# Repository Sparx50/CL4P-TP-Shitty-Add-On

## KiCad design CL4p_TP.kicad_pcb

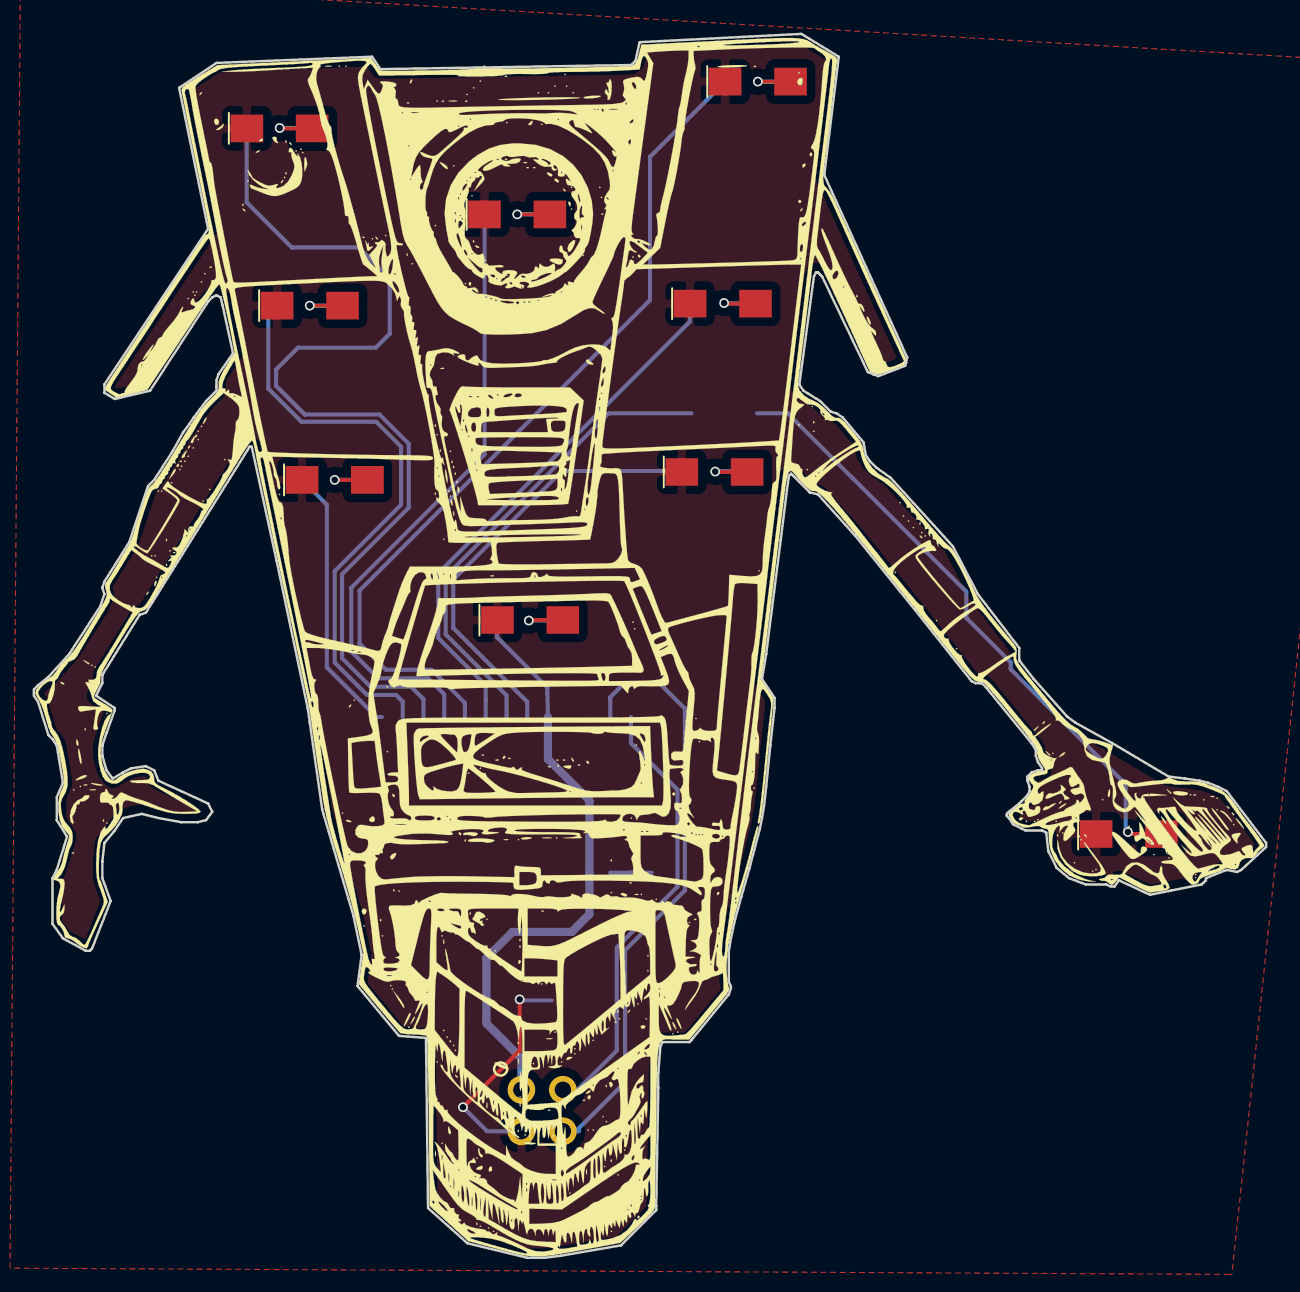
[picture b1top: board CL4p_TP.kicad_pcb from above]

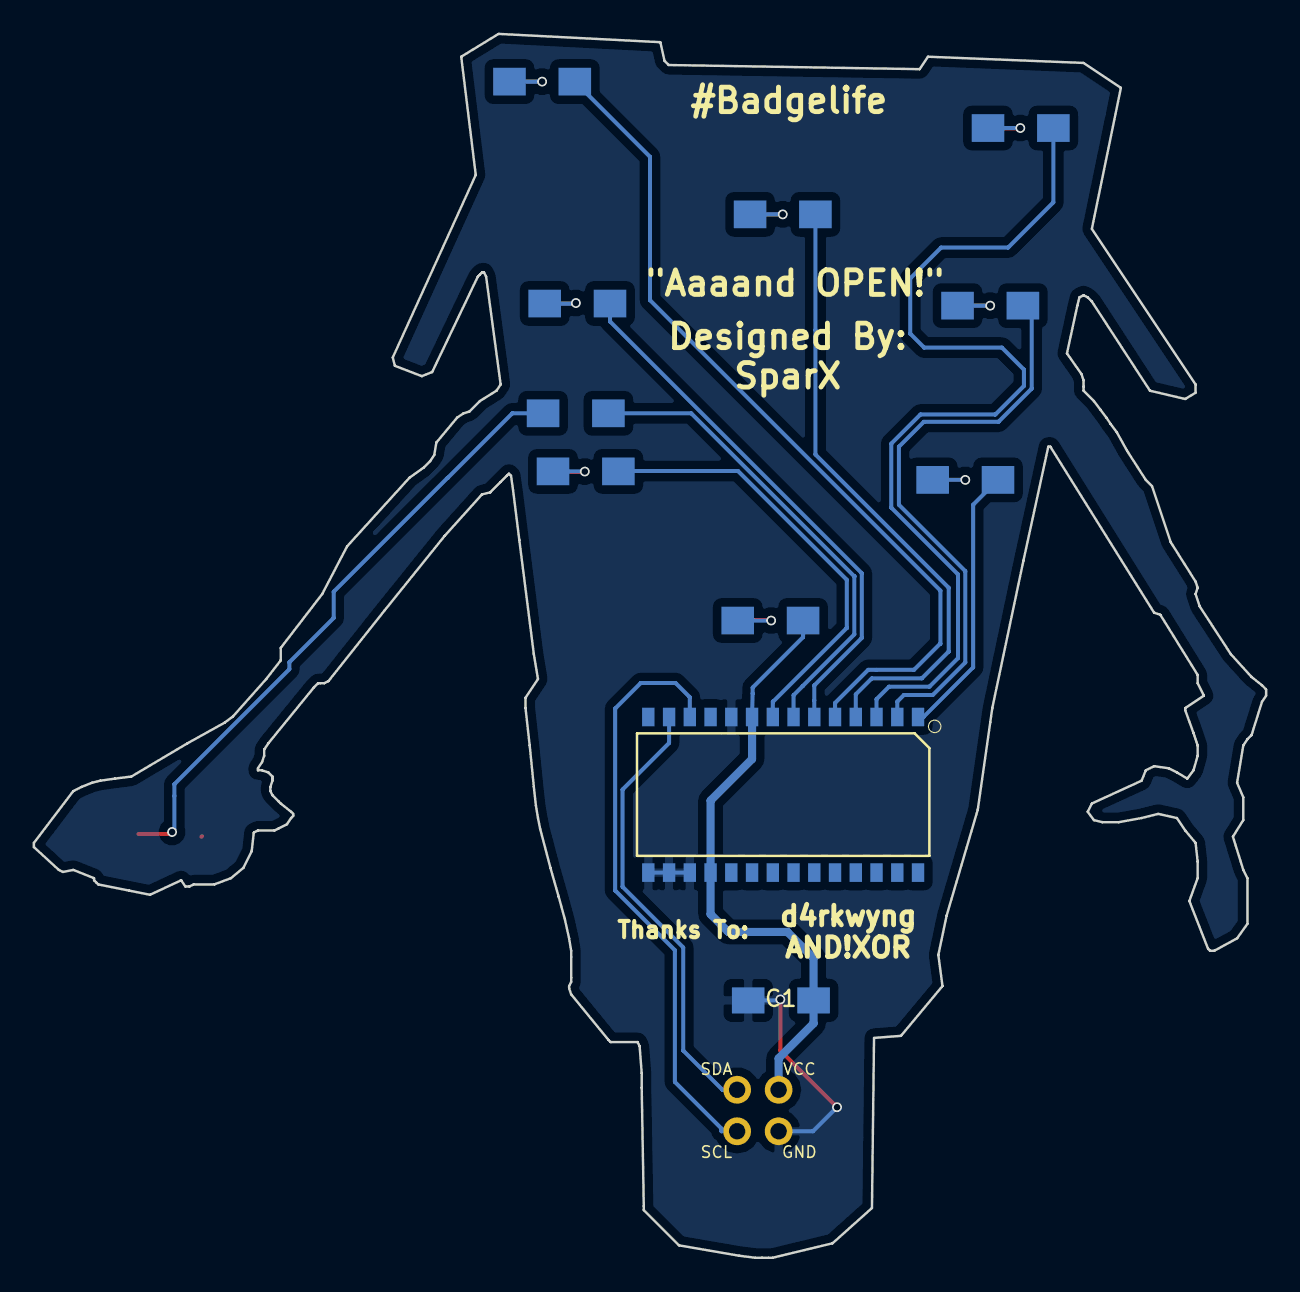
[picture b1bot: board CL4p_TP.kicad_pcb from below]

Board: 2 copper layers, 75.4 x 74.9 mm, 21 parts (11 on the bottom side), 21 nets.

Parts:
C1: 0.1uf; C_1206_HandSoldering_Min_Silk
D1, D2, D3, D4, D5, D6, D7, D8, D9: LED; LED_1206_HandSoldering_Min
R1, R2, R3, R4, R5, R6, R7, R8, R9: 220; R_1206_HandSoldering_Min
U1: MCP23017; MCP23017-ESO_NoSilk
X1: Badgelife_shitty_connector; Badgelife-Shitty-2x2

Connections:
+3V3: C1.1, R8.2, U1.9, U1.18, X1.1
GND: C1.2, D1.1, D2.1, D3.1, D4.1, D5.1, D6.1, D7.1, D8.1, D9.1, U1.10, U1.15, U1.16, U1.17, X1.2
unnamed: D1.2, R1.2
unnamed: D2.2, R2.2
unnamed: D3.2, R3.2
unnamed: D4.2, R4.2
unnamed: D5.2, R5.2
unnamed: D6.2, R6.2
unnamed: D7.2, R7.2
unnamed: D8.2, R8.1
unnamed: D9.2, R9.2
unnamed: R1.1, U1.1
unnamed: R2.1, U1.2
unnamed: R3.1, U1.3
unnamed: R4.1, U1.4
unnamed: R5.1, U1.5
unnamed: R6.1, U1.6
unnamed: R7.1, U1.7
unnamed: R9.1, U1.8
scl: U1.12, X1.3
sda: U1.13, X1.4

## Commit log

2018-06-06 Leaps and bounds
    Finished Cut, Passed sanity check and added silkscreen to credit assistance
2018-06-21 Rev.2
    Generated new gerbers for rev. 2.
    Includes
    -cleaned up paths utilizing ground plane and a larger plane between 3.3,Capacitor and MCP23017 Chip
    -changed the mcp23017 chip from SOIC to SSOP
    -modified single LED in middle of the board to recieve power directly off of the badge(just in case there is no I2C communication).
2018-06-29 SSOP style_Final
    Final Boardtype for SSOP style MCP23017
2019-05-16 Tidying up
    Uploading Copy used for final production
